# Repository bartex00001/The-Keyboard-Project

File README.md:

# The Keyboard Project  

Documentation can be found here:  
[Notion - The Keyboard Project](https://stefbart.notion.site/The-Keyboard-Project-20efdf3d025f40b1b14f3d861e6cc41f)

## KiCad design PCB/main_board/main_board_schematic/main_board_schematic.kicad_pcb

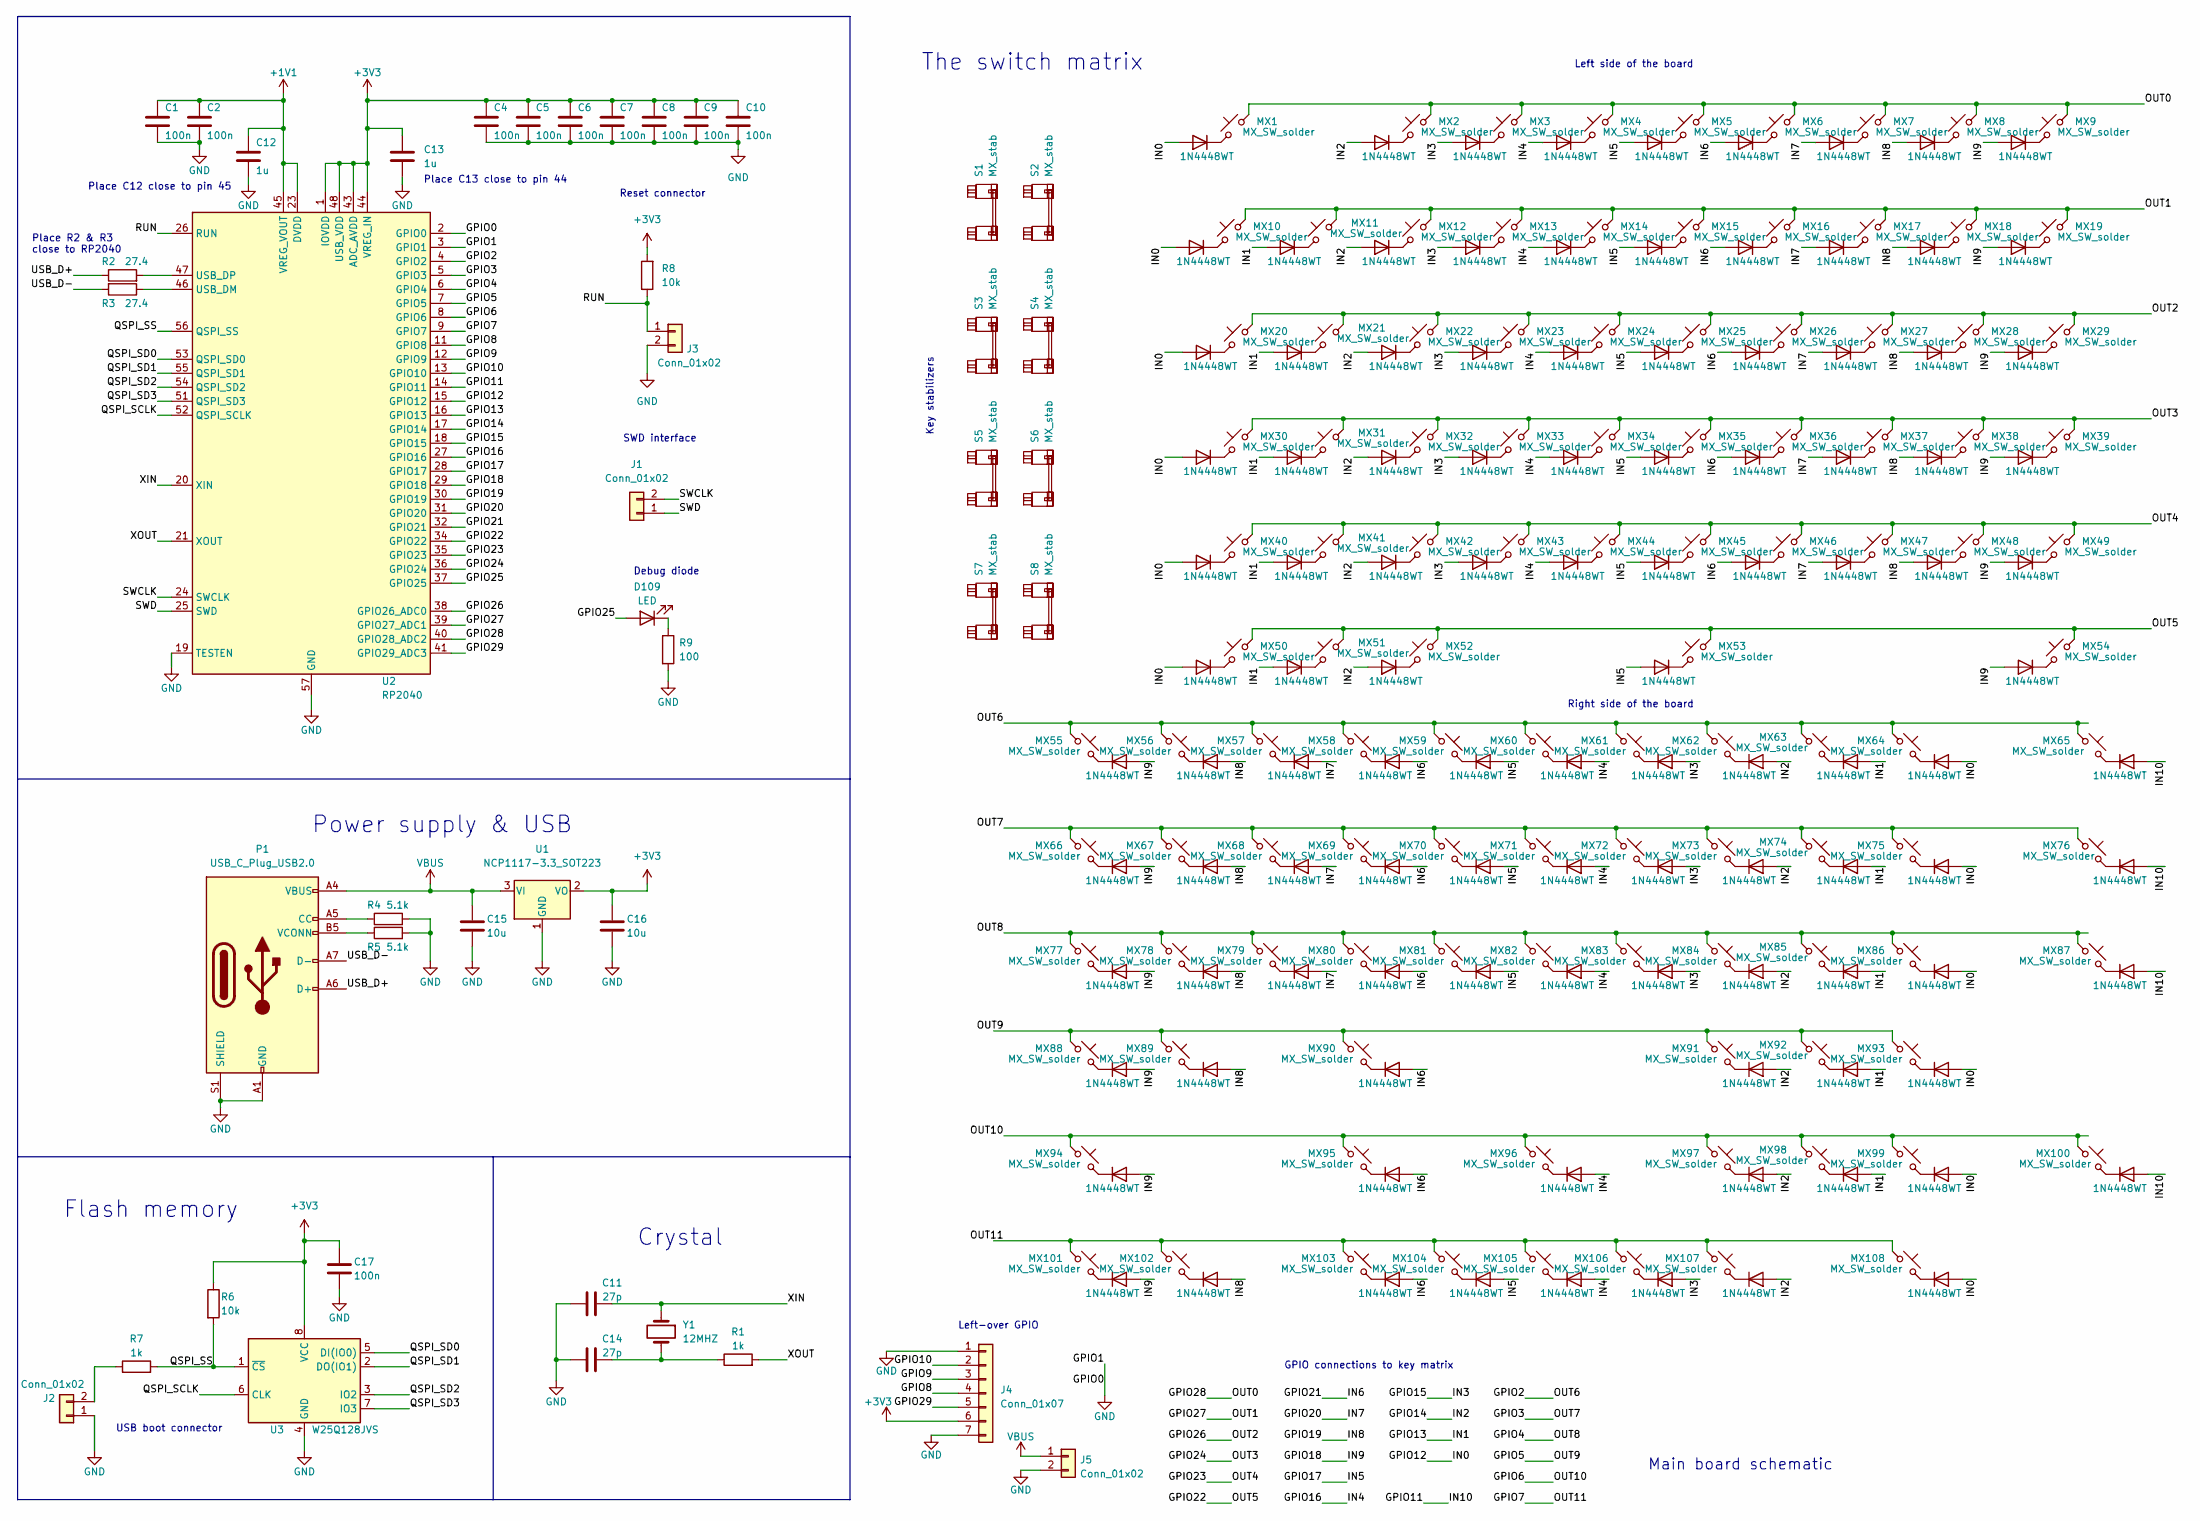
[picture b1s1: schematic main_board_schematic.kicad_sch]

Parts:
C1, C2, C4, C5, C6, C7, C8, C9, C10, C17: 100n; C_0603_1608Metric
C11, C14: 27p; C_0603_1608Metric
C12, C13: 1u; C_0603_1608Metric
C15, C16: 10u; C_0603_1608Metric
D1, D2, D3, D4, D5, D6, D7, D8, D9, D10, D11, D12, D13, D14, D15, D16, D17, D18, D19, D20, D21, D22, D23, D24, D25, D26, D27, D28, D29, D30, D31, D32, D33, D34, D35, D36, D37, D38, D39, D40, D41, D42, D43, D44, D45, D46, D47, D48, D49, D50, D51, D52, D53, D54, D55, D56, D57, D58, D59, D60, D61, D62, D63, D64, D65, D66, D67, D68, D69, D70, D71, D72, D73, D74, D75, D76, D77, D78, D79, D80, D81, D82, D83, D84, D85, D86, D87, D88, D89, D90, D91, D92, D93, D94, D95, D96, D97, D98, D99, D100, D101, D102, D103, D104, D105, D106, D107, D108: 1N4448WT; D_SOD-523
D109: LED; LED_0603_1608Metric
J1, J2, J3, J5: Conn_01x02; PinHeader_1x02_P2.54mm_Vertical
J4: Conn_01x07; PinHeader_1x07_P2.54mm_Vertical
MX1, MX2, MX3, MX4, MX5, MX6, MX7, MX8, MX9, MX10, MX11, MX12, MX13, MX14, MX15, MX16, MX17, MX18, MX19, MX21, MX22, MX23, MX24, MX25, MX26, MX27, MX28, MX29, MX31, MX32, MX33, MX34, MX35, MX36, MX37, MX38, MX39, MX40, MX41, MX42, MX43, MX44, MX45, MX46, MX47, MX48, MX49, MX53, MX55, MX56, MX57, MX58, MX59, MX60, MX61, MX62, MX63, MX64, MX65, MX66, MX67, MX68, MX69, MX70, MX71, MX72, MX73, MX74, MX75, MX76, MX77, MX78, MX79, MX81, MX82, MX83, MX84, MX85, MX86, MX87, MX88, MX89, MX90, MX91, MX92, MX93, MX94, MX95, MX96, MX97, MX98, MX99, MX100, MX104, MX105, MX106, MX107, MX108: MX_SW_solder; SW_MX_1u
MX20, MX80: MX_SW_solder; SW_MX_1.5u
MX30: MX_SW_solder; SW_MX_1.75u
MX50, MX51, MX52, MX54, MX101, MX102, MX103: MX_SW_solder; SW_MX_1.25u
P1: USB_C_Plug_USB2.0; USB_C_Receptacle_G-Switch_GT-USB-7010ASV
R1, R7: 1k; R_0603_1608Metric
R2, R3: 27.4; R_0603_1608Metric
R4, R5: 5.1k; R_0603_1608Metric
R6, R8: 10k; R_0603_1608Metric
R9: 100; R_0603_1608Metric
S1: MX_stab; STAB_MX_P_6.25u
S2, S5: MX_stab; STAB_MX_P_2.25u
S3, S4, S7, S8: MX_stab; STAB_MX_P_2u
S6: MX_stab; STAB_MX_P_2.75u
U1: NCP1117-3.3_SOT223; SOT-223-3_TabPin2
U2: RP2040; QFN-56-1EP_7x7mm_P0.4mm_EP3.2x3.2mm
U3: W25Q128JVS; SOIC-8_5.23x5.23mm_P1.27mm
Y1: 12MHZ; Crystal_HC49-U_Vertical

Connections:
+1V1: C1.1, C2.1, C12.1, U2.23 (DVDD), U2.45 (VREG_VOUT), U2.50 (DVDD)
+3V3: C4.1, C5.1, C6.1, C7.1, C8.1, C9.1, C10.1, C13.1, C16.1, C17.1, J4.6, R6.1, R8.2, U1.2 (VO), U2.1 (IOVDD), U2.10 (IOVDD), U2.22 (IOVDD), U2.33 (IOVDD), U2.42 (IOVDD), U2.43 (ADC_AVDD), U2.44 (VREG_IN), U2.48 (USB_VDD), U2.49 (IOVDD), U3.8 (VCC)
/GPIO2: MX55.2, MX56.2, MX57.2, MX58.2, MX59.2, MX60.2, MX61.2, MX62.2, MX63.2, MX64.2, MX65.2, U2.4 (GPIO2)
/GPIO3: MX66.2, MX67.2, MX68.2, MX69.2, MX70.2, MX71.2, MX72.2, MX73.2, MX74.2, MX75.2, MX76.2, U2.5 (GPIO3)
/GPIO4: MX77.2, MX78.2, MX79.2, MX80.2, MX81.2, MX82.2, MX83.2, MX84.2, MX85.2, MX86.2, MX87.2, U2.6 (GPIO4)
/GPIO5: MX88.2, MX89.2, MX90.2, MX91.2, MX92.2, MX93.2, U2.7 (GPIO5)
/GPIO6: MX94.2, MX95.2, MX96.2, MX97.2, MX98.2, MX99.2, MX100.2, U2.8 (GPIO6)
/GPIO7: MX101.2, MX102.2, MX103.2, MX104.2, MX105.2, MX106.2, MX107.2, MX108.2, U2.9 (GPIO7)
/GPIO8: J4.4, U2.11 (GPIO8)
/GPIO9: J4.3, U2.12 (GPIO9)
/GPIO10: J4.2, U2.13 (GPIO10)
/GPIO11: D65.2 (A), D76.2 (A), D87.2 (A), D100.2 (A), U2.14 (GPIO11)
/GPIO12: D1.2 (A), D10.2 (A), D20.2 (A), D30.2 (A), D40.2 (A), D50.2 (A), D64.2 (A), D75.2 (A), D86.2 (A), D93.2 (A), D99.2 (A), D108.2 (A), U2.15 (GPIO12)
/GPIO13: D11.2 (A), D21.2 (A), D31.2 (A), D41.2 (A), D51.2 (A), D63.2 (A), D74.2 (A), D85.2 (A), D92.2 (A), D98.2 (A), U2.16 (GPIO13)
/GPIO14: D2.2 (A), D12.2 (A), D22.2 (A), D32.2 (A), D42.2 (A), D52.2 (A), D62.2 (A), D73.2 (A), D84.2 (A), D91.2 (A), D97.2 (A), D107.2 (A), U2.17 (GPIO14)
/GPIO15: D3.2 (A), D13.2 (A), D23.2 (A), D33.2 (A), D43.2 (A), D61.2 (A), D72.2 (A), D83.2 (A), D106.2 (A), U2.18 (GPIO15)
/GPIO16: D4.2 (A), D14.2 (A), D24.2 (A), D34.2 (A), D44.2 (A), D60.2 (A), D71.2 (A), D82.2 (A), D96.2 (A), D105.2 (A), U2.27 (GPIO16)
/GPIO17: D5.2 (A), D15.2 (A), D25.2 (A), D35.2 (A), D45.2 (A), D53.2 (A), D59.2 (A), D70.2 (A), D81.2 (A), D104.2 (A), U2.28 (GPIO17)
/GPIO18: D9.2 (A), D19.2 (A), D29.2 (A), D39.2 (A), D49.2 (A), D54.2 (A), D55.2 (A), D66.2 (A), D77.2 (A), D88.2 (A), D94.2 (A), D101.2 (A), U2.29 (GPIO18)
/GPIO19: D8.2 (A), D18.2 (A), D28.2 (A), D38.2 (A), D48.2 (A), D56.2 (A), D67.2 (A), D78.2 (A), D89.2 (A), D102.2 (A), U2.30 (GPIO19)
/GPIO20: D7.2 (A), D17.2 (A), D27.2 (A), D37.2 (A), D47.2 (A), D57.2 (A), D68.2 (A), D79.2 (A), U2.31 (GPIO20)
/GPIO21: D6.2 (A), D16.2 (A), D26.2 (A), D36.2 (A), D46.2 (A), D58.2 (A), D69.2 (A), D80.2 (A), D90.2 (A), D95.2 (A), D103.2 (A), U2.32 (GPIO21)
/GPIO22: MX50.2, MX51.2, MX52.2, MX53.2, MX54.2, U2.34 (GPIO22)
/GPIO23: MX40.2, MX41.2, MX42.2, MX43.2, MX44.2, MX45.2, MX46.2, MX47.2, MX48.2, MX49.2, U2.35 (GPIO23)
/GPIO24: MX30.2, MX31.2, MX32.2, MX33.2, MX34.2, MX35.2, MX36.2, MX37.2, MX38.2, MX39.2, U2.36 (GPIO24)
/GPIO25: D109.2 (A), U2.37 (GPIO25)
/GPIO26: MX20.2, MX21.2, MX22.2, MX23.2, MX24.2, MX25.2, MX26.2, MX27.2, MX28.2, MX29.2, U2.38 (GPIO26_ADC0)
/GPIO27: MX10.2, MX11.2, MX12.2, MX13.2, MX14.2, MX15.2, MX16.2, MX17.2, MX18.2, MX19.2, U2.39 (GPIO27_ADC1)
/GPIO28: MX1.2, MX2.2, MX3.2, MX4.2, MX5.2, MX6.2, MX7.2, MX8.2, MX9.2, U2.40 (GPIO28_ADC2)
/GPIO29: J4.5, U2.41 (GPIO29_ADC3)
/QSPI_SCLK: U2.52 (QSPI_SCLK), U3.6 (CLK)
/QSPI_SD0: U2.53 (QSPI_SD0), U3.5 (DI(IO0))
/QSPI_SD1: U2.55 (QSPI_SD1), U3.2 (DO(IO1))
/QSPI_SD2: U2.54 (QSPI_SD2), U3.3 (IO2)
/QSPI_SD3: U2.51 (QSPI_SD3), U3.7 (IO3)
/QSPI_SS: R6.2, R7.2, U2.56 (QSPI_SS), U3.1 (~CS)
/RUN: J3.1, R8.1, U2.26 (RUN)
/SWCLK: J1.2, U2.24 (SWCLK)
/SWD: J1.1, U2.25 (SWD)
/USB_D+: P1.A6 (D+), R2.1
/USB_D-: P1.A7 (D-), R3.2
/XIN: C11.1, U2.20 (XIN), Y1.1
/XOUT: R1.2, U2.21 (XOUT)
GND: C1.2, C2.2, C4.2, C5.2, C6.2, C7.2, C8.2, C9.2, C10.2, C11.2, C12.2, C13.2, C14.1, C15.2, C16.2, C17.2, J2.1, J3.2, J4.1, J4.7, J5.2, P1.A1 (GND), P1.A12 (GND), P1.B1 (GND), P1.B12 (GND), P1.S1 (SHIELD), R4.2, R5.2, R9.2, U1.1 (GND), U2.2 (GPIO0), U2.3 (GPIO1), U2.19 (TESTEN), U2.57 (GND), U3.4 (GND)
unnamed: C14.2, R1.1, Y1.2
unnamed: D1.1 (K), MX1.1
unnamed: D2.1 (K), MX2.1
unnamed: D3.1 (K), MX3.1
unnamed: D4.1 (K), MX4.1
unnamed: D5.1 (K), MX5.1
unnamed: D6.1 (K), MX6.1
unnamed: D7.1 (K), MX7.1
unnamed: D8.1 (K), MX8.1
unnamed: D9.1 (K), MX9.1
unnamed: D10.1 (K), MX10.1
unnamed: D11.1 (K), MX11.1
unnamed: D12.1 (K), MX12.1
unnamed: D13.1 (K), MX13.1
unnamed: D14.1 (K), MX14.1
unnamed: D15.1 (K), MX15.1
unnamed: D16.1 (K), MX16.1
unnamed: D17.1 (K), MX17.1
unnamed: D18.1 (K), MX18.1
unnamed: D19.1 (K), MX19.1
unnamed: D20.1 (K), MX20.1
unnamed: D21.1 (K), MX21.1
unnamed: D22.1 (K), MX22.1
unnamed: D23.1 (K), MX23.1
unnamed: D24.1 (K), MX24.1
unnamed: D25.1 (K), MX25.1
unnamed: D26.1 (K), MX26.1
unnamed: D27.1 (K), MX27.1
unnamed: D28.1 (K), MX28.1
unnamed: D29.1 (K), MX29.1
unnamed: D30.1 (K), MX30.1
unnamed: D31.1 (K), MX31.1
unnamed: D32.1 (K), MX32.1
unnamed: D33.1 (K), MX33.1
unnamed: D34.1 (K), MX34.1
unnamed: D35.1 (K), MX35.1
unnamed: D36.1 (K), MX36.1
unnamed: D37.1 (K), MX37.1
unnamed: D38.1 (K), MX38.1
unnamed: D39.1 (K), MX39.1
unnamed: D40.1 (K), MX40.1
unnamed: D41.1 (K), MX41.1
unnamed: D42.1 (K), MX42.1
unnamed: D43.1 (K), MX43.1
unnamed: D44.1 (K), MX44.1
unnamed: D45.1 (K), MX45.1
unnamed: D46.1 (K), MX46.1
unnamed: D47.1 (K), MX47.1
unnamed: D48.1 (K), MX48.1
unnamed: D49.1 (K), MX49.1
unnamed: D50.1 (K), MX50.1
unnamed: D51.1 (K), MX51.1
unnamed: D52.1 (K), MX52.1
unnamed: D53.1 (K), MX53.1
unnamed: D54.1 (K), MX54.1
unnamed: D55.1 (K), MX55.1
unnamed: D56.1 (K), MX56.1
unnamed: D57.1 (K), MX57.1
unnamed: D58.1 (K), MX58.1
unnamed: D59.1 (K), MX59.1
unnamed: D60.1 (K), MX60.1
unnamed: D61.1 (K), MX61.1
unnamed: D62.1 (K), MX62.1
unnamed: D63.1 (K), MX63.1
unnamed: D64.1 (K), MX64.1
unnamed: D65.1 (K), MX65.1
unnamed: D66.1 (K), MX66.1
unnamed: D67.1 (K), MX67.1
unnamed: D68.1 (K), MX68.1
unnamed: D69.1 (K), MX69.1
unnamed: D70.1 (K), MX70.1
unnamed: D71.1 (K), MX71.1
unnamed: D72.1 (K), MX72.1
unnamed: D73.1 (K), MX73.1
unnamed: D74.1 (K), MX74.1
unnamed: D75.1 (K), MX75.1
unnamed: D76.1 (K), MX76.1
unnamed: D77.1 (K), MX77.1
unnamed: D78.1 (K), MX78.1
unnamed: D79.1 (K), MX79.1
unnamed: D80.1 (K), MX80.1
unnamed: D81.1 (K), MX81.1
unnamed: D82.1 (K), MX82.1
unnamed: D83.1 (K), MX83.1
unnamed: D84.1 (K), MX84.1
unnamed: D85.1 (K), MX85.1
unnamed: D86.1 (K), MX86.1
unnamed: D87.1 (K), MX87.1
unnamed: D88.1 (K), MX88.1
unnamed: D89.1 (K), MX89.1
unnamed: D90.1 (K), MX90.1
unnamed: D91.1 (K), MX91.1
unnamed: D92.1 (K), MX92.1
unnamed: D93.1 (K), MX93.1
unnamed: D94.1 (K), MX94.1
unnamed: D95.1 (K), MX95.1
unnamed: D96.1 (K), MX96.1
unnamed: D97.1 (K), MX97.1
unnamed: D98.1 (K), MX98.1
unnamed: D99.1 (K), MX99.1
unnamed: D100.1 (K), MX100.1
unnamed: D101.1 (K), MX101.1
unnamed: D102.1 (K), MX102.1
unnamed: D103.1 (K), MX103.1
unnamed: D104.1 (K), MX104.1
unnamed: D105.1 (K), MX105.1
unnamed: D106.1 (K), MX106.1
unnamed: D107.1 (K), MX107.1
unnamed: D108.1 (K), MX108.1
unnamed: D109.1 (K), R9.1
unnamed: J2.2, R7.1
unnamed: P1.A5 (CC), R4.1
unnamed: P1.B5 (VCONN), R5.1
unnamed: R3.1, U2.46 (USB_DM)
unnamed: R2.2, U2.47 (USB_DP)
VBUS: C15.1, J5.1, P1.A4 (VBUS), P1.A9 (VBUS), P1.B4 (VBUS), P1.B9 (VBUS), U1.3 (VI)

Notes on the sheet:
Debug diode
USB boot connector
Crystal
Right side of the board
Key stabilizers
Place R2 & R3 close to RP2040
Place C13 close to pin 44
Place C12 close to pin 45
Main board schematic
Left side of the board
GPIO connections to key matrix
Reset connector
SWD interface
Left-over GPIO
Flash memory
The switch matrix
Power supply & USB

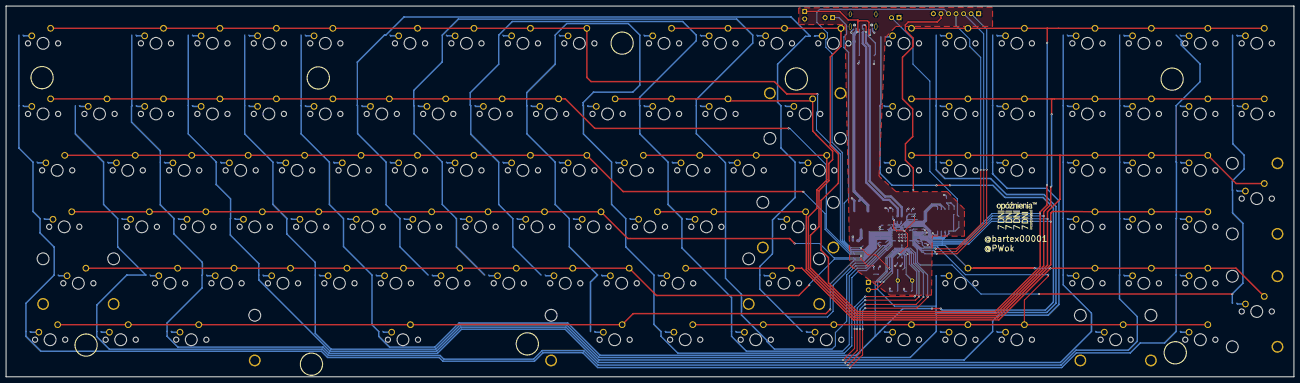
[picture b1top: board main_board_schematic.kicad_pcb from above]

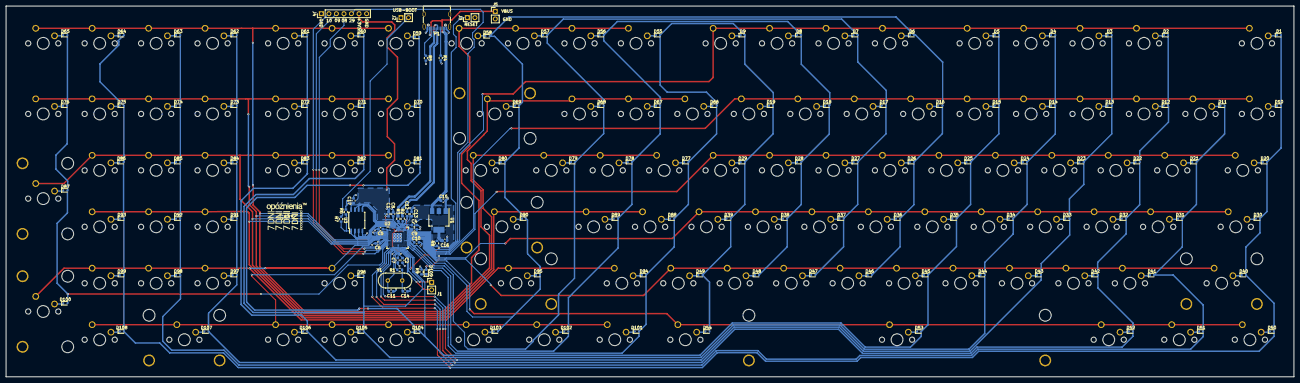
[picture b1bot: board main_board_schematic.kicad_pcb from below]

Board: 2 copper layers, 434.6 x 125.1 mm, 260 parts (144 on the bottom side), 160 nets.

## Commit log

2022-11-14 Updated readme with a link to Notion
2022-11-14 Fine-tuned the link to documentation
2022-11-20 Created a schematic for a switch matrix
2022-11-20 Image of built prototype switch matrix
2022-11-26 Created kayboard layout and matrix lines
2022-11-27 Created functioning hello world setup
2022-11-27 Added a readme to Keyboard Driver
2022-11-27 Cleaned the CMakeLists
2022-12-02 Created a 'how to build' guide
2022-12-02 Removed unnecessary divider lines
2022-12-02 Removed unnecessary comments from config files
2023-05-06 Prototype now better represents the schematic
2023-05-06 Renamed schematic components
2023-05-07 Small update to docs
2023-05-11 Created new kiCad project for the board and added basic components for power supply
2023-05-12 Added pull downs for cc and vconn
2023-05-12 Fixed wiring mistake...
2023-05-13 Added debugging section to readme
2023-05-13 Turned of uart support
2023-05-14 Added label for power supply and usb
2023-05-14 Created the crystal oscilator
2023-05-14 Project organisation - added photos of circuit sections and a title
2023-05-14 Created a schematic for the flash storage
2023-05-14 Moved the components around 'minor changes'
2023-05-15 Added rp2040 alongside some components
2023-05-16 Added all the siwtches to the board
2023-05-16 Moved to kicad7 and added key stabilizers
2023-05-16 Added images of rp2040 and switch matrix
2023-05-16 Added labels to the stabilizers
2023-05-17 Added footprints for all components
2023-05-17 Ignore .zip files
2023-05-17 Chenged the chematic switches to mx-switches
2023-05-20 Placed large portion of the diodes
2023-05-21 Added all diodes to key matrix
2023-05-21 placed the rp2040 inside the board
2023-05-24 Placed and connected all components
2023-05-25 Connected matrix to the rp2040
2023-05-30 Moved usb-c connector and added labels
2023-05-30 Added a led connected to pin25
2023-05-30 Exposed pins and power rails
2023-05-30 Created logo with transparent background and a kicad lib file
2023-05-30 Fixed footprints for pins
2023-06-07 New CMake structure for keyboard driver
2023-06-07 Created initializer for key matrix pins
2023-06-07 Created a mock program to read keys pressed on a matrix
2023-06-09 Added list of usb hid key-codes
2023-06-09 Key matrix now holds 'key' objects
2023-06-11 Updated command path in readme
2023-06-13 Added generated keyboard hid description
2023-06-25 Added configuration files
2023-06-25 Updated build settings
2023-06-25 File replaced by 'usbDescriptors.hpp/cpp'
2023-06-25 Updated main loop to send 'a' key press every second
2023-06-28 Created a buffer manager - for managing the buffer...
2023-06-28 Removed some functions from the header
2023-06-28 Moved buffer-sending to BufferManager
2023-06-28 Moved key-scanning task to KeyMatrix
2023-07-03 Placed text and 7DL logo on pcb
2023-07-03 Added logo to the back side of pcb
2023-07-03 Added silcscreen guide to where holes can be drilled
2023-09-16 Update README.md cmake install command
